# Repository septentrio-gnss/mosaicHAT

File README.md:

# mosaicHAT

mosaicHAT: A GNSS HAT for Raspberry PI </br>
Author: <a href="https://github.com/Jamalhazem98">Jamal Sa'd</a>  </br>
Maintainer: (Septentrio gnss github user) <githubuser@septentrio.com> </br>
External website: https://github.com/septentrio-gnss/mosaicHAT </br>
License: <a href="https://creativecommons.org/licenses/by-sa/4.0/">Creative Commons Attribution Share-Alike License.</a> and <a href="https://www.oshwa.org/definition/">Open Source HW</a> </br>
Available for purchase here: https://www.ardusimple.com/product/septentrio-mosaichat/ </br>

Click to watch this video introducing mosaicHAT

Table of contents
=================
<!--ts-->
   * [Introduction to mosaicHAT](#introduction-to-mosaichat)
      * [What is mosaicHAT?](#what-is-mosaichat)
      * [A HAT for Raspberry Pi?](#a-hat-for-raspberry-pi)
      * [What is the mosaic module?](#what-is-the-mosaic-module)
      * [Who is Septentrio?](#who-is-septentrio)
      * [Is the project Open Source?](#is-the-project-open-source)
      * [mosaicHAT News](#mosaicHAT-News)
      * [Disclaimer](#disclaimer)
   * [mosaicHAT user documentation](#mosaichat-user-documentation)
      * [mosaicHAT Manufacturing and Assembly](#mosaichat-manufacturing-and-assembly)
      * [General interfaces of mosaicHAT](#General-interfaces-of-mosaichat)
      * [Connecting to Raspberry Pi](#connecting-to-raspberry-pi)
      * [Connecting an antenna](#connecting-an-antenna)
      * [USB Communication](#usb-communication)
      * [Serial Communication](#serial-communication)
      * [FTDI-connector](#ftdi-connector)
      * [Indicator LEDs](#indicator-leds)
      * [Reset mosaic](#reset-mosaic)
      * [PPS Output](#pps-output)
      * [Events](#events)
      * [Python Script](#python-script)
      * [ROS support with ROSaic](#ros-support-with-rosaic)
      * [Arduino support for mosaicHAT](#arduino-support-for-mosaichat)
      * [Using the Fritzing Schematics](#using-the-fritzing-schematics)
   * [mosaicHAT Design documentation](#mosaichat-design-documentation)
      * [mosaic Pinout](#mosaic-pinout)
      * [Power Sources](#power-sources)
      * [Antennas](#antennas)
      * [Raspberry Pi Serial](#raspberry-pi-serial)
      * [Reset Input](#reset-input)
      * [Micro USB](#micro-usb)
      * [Events and PPSO](#events-and-ppso)
      * [FTDI](#ftdi)
      * [LEDs](#leds)
      * [Clock Frequency Reference ](#clock-frequency-reference )
   * [Further improvements](#further-improvements)
   
<!--te-->

## Introduction to mosaicHAT
### What is mosaicHAT?
The mosaicHAT is an Open Source GPS/GNSS HW PCB HAT which integrates <a href="https://www.septentrio.com/en/products/gnss-receivers/rover-base-receivers/receivers-module/mosaic">Septentrio's mosaic-X5</a> GNSS module (and other Septentrio pin compatible modules) with basic communications and which can be stacked into a Raspberry Pi system. 

The goal of the design is to allow easy HW prototyping using the mosaic-X5 GNSS module taking the advantage of the computer ecosystem provided by the Raspberry Pi environment. The board however can also be used standalone since it can be powered either via USB or via power pins. 
This project and design can be used either produced with your local electronics assembly house or can also be used as a starting point for your own HW integrations.

### A HAT for Raspberry Pi?
HAT stands for “Hardware Attached on Top”. It is a new hardware specification for add-one modules for the new Raspberry Pi model B+. HATs have several advantages compared to older add-on modules for the Raspberry Pi.

#### Robust mechanical design
With 4 mounting holes the connection between the Raspberry Pi and the add-on board is very robust. 

### Can I buy it?
#### Buy at Ardusimple now
Yes, the mosaicHAT can now be purchased from Ardusimple directly. Ardusimple is a company which produces easy to use GNSS RTK systems. They can sell the mosaicHAT directly as well as other mosaic based GNSS boards.
</br>
Website: https://www.ardusimple.com/product/septentrio-mosaichat/

#### Produce yourself
You can also use the reference design, layout and Bill Of Materials from this project and contact your local manufacturing company for producing it (no restrictions). Within this project we have used [Eurocircuits](https://www.eurocircuits.com/) who can be quite fast in producing a board for you (both PCB and assembly can be done by them). Section [mosaicHAT Manufacturing and Assembly](#mosaichat-manufacturing-and-assembly)

##### Do I need to source special components for producing this board?
Not really, most of the components are generic enough. All components used are available on Digi-Key and clearly listed in the project's Bill Of Materials. The mosaic GNSS module can be obtained from Digikey or directly from Septentrio. Should your project be larger then we recommend you to contact Septentrio sales team directly at <a href="https://www.septentrio.com/en/contact/ask-question">Septentrio Contact Page</a>.

### What is the mosaic module?
#### mosaic-X5
<a href="https://www.septentrio.com/en/products/gnss-receivers/rover-base-receivers/receivers-module/mosaic">Septentrio's mosaic-X5</a>, a multi-band, multi-constellation GNSS receiver in a low power surface mount module with a wide array of interfaces, designed for mass market applications like robotics and autonomous systems, capable of tracking all Global Navigation Satellite System (GNSS) constellations supporting current and future signals. With unique built-in AIM+ technology for interference mitigation, Septentrio is offering a performance benchmark in mass market GNSS positioning building blocks.

#### Other mosaic versions

Any <a href="https://web.septentrio.com/GH-SSN-modules c">other mosaic pin compatible products</a> could also be used on this design, however you would need to take into consideration the functions or pins which would need to exposed and then modify the design for your own project. Surely feel free to spin of the project and refer to this one should you make other open source designs based on mosaicHAT.

### Who is Septentrio?

Septentrio designs, manufactures and sells high-precision, multi-frequency, multi-constellation GPS/GNSS equipment for use in demanding applications. Septentrio products are used in a wide variety of industries including marine, construction, precision agriculture, logistics, machine control, rail, automotive, survey and mapping, geographic information systems (GIS), unmanned aerial vehicles (UAVs) and scientific. Septentrio receivers deliver consistently accurate and precise GNSS positioning scalable to centimeter-level and designed to perform solidly in the most challenging environments. Septentrio receivers are available as OEM boards, housed receivers and smart antennas.

The technology offers high accuracy and reliability thanks to GNSS+ algorithms as well as <a href="https://www.septentrio.com/en/advanced-interference-monitoring-mitigation-aim">Septentrio's Advanced Interference Monitoring and Mitigation (AIM+)</a> which protects against RF interference (jamming) and spoofing.

For more information about Septentrio products go to [**https://www.septentrio.com/**](https://web.septentrio.com/GH-SSN-home).

### Deliverables
This project makes the following deliverables for both integrators and designers of systems around Septentrio's mosaic modules.

|File|Description|
|--------|----------|
|KiCAD_files/HATv1.0.pro| KiCAD project |
|KiCAD_files/HATv1.0.kicad_pcb | KiCAD layout |
|KiCAD_files/HATv1.0.sch| KiCAD schematic |
|KiCAD_files/mosaicHAT_library.lib| Project schematic library |
|mosaic_design_components/mosaic_X5.mosaic-X5.lib | mosaic symbol |
|mosaic_design_components/mosaic_X5.kicad_mod| mosaic footprint |
|mosaic_design_components/mosaic3D.stp| mosaic 3D object |
|BOM/mosaicHAT_BOM.xlsx| mosaicHAT Bill of Materials |
|Fritzing/mosaicHAT.fzpz| mosaicHAT Fritzing part |
|Fritzing/mosaicHAT_Graphic.svg| mosaicHAT SVG |

### Is the project open source?
Yes, as it allows easy adaptations and thus enables the robotics and autonomous community to create their own spin off projects.
As such this can be also a starting reference point for integrators when in need of GNSS integration.

With open source it means that the following is provided:
-Editable source files
-Modifications and spin off projects allowed
-You are allowed to sell your version. No -NC limitations.
-May require attribution
-We encourage you to stand on our shoulders and even make money at it! 

More info about licensing can be found here: 
<a href="https://creativecommons.org/licenses/by-sa/4.0/">Creative Commons Attribution Share-Alike License.</a> and <a href="https://www.oshwa.org/definition/">Open Source HW</a>

### mosaicHAT News
 
#### Survey-grade GNSS receiver based on mosaicHAT, by Chiba Institue of Technologyy.
Low-cost survey-grade GNSS mosaicHAT Station built by Prof. Suzuki from Chiba Institute Of Technology, Japan. The receiver comes with touch display to use the webUI of Septentrio mosaic-X5 GNSS module receiver. Click to visit the project's github repo.

#### Drive test to Dead Sea with RTK corrections 
mosaicHAT has been taken in a GNSS/RTK drive to the lowest point on earth's land - The Dead Sea (-400m Sea Level).
Click to watch the journey on Youtube:

### Disclaimer

This project is **PROVIDED AS IS** and while the general interfaces have been tested, the project has not been fully validated nor by the author nor by Septentrio.
It remains your responsibility when producing or using this design for your own purposes.
We recommend you to contact Septentrio should you have questions on how to integrate Septentrio's GNSS mosaic modules.

Their support web site is <http://www.septentrio.com/support> </br>.

### Documentation sections
This project contains two important sections for documentation. The first one which is a user documentation (see section [mosaicHAT user documentation](#mosaichat-user-documentation)) and the second one (see section [mosaicHAT Design documentation](#mosaichat-design-documentation)) which is a documentation for designers wanting to modify the reference design of this project.

## mosaicHAT user documentation
### mosaicHAT Manufacturing and Assembly
You can use the reference design, layout and Bill Of Materials files from this project and contact your local manufacturing company for producing it. Within this project we have used [Eurocircuits](https://www.eurocircuits.com/) who can be quite fast in producing a board  (both PCB and assembly can be done by them).

#### Elements to provide when manufacturing the board

If you decided to make the board through a PCB manufacturing service, they will ask for the following parts:

For manufacturing the board:

- Layout design (Some services accept native KiCAD files, otherwise you will need to export the layout to the standard Gerber format).

For assembly:

- Bill of Materials (BOM), the list of used electronic components alongside with their reference designators. For our project, check [mosaicHAT BOM](BOM/mosaicHAT_BOM.xlsx).
- Component Placement List (CPL), the exact position of each component on the board (X,Y and Rotation). CPL could be exported from KiCAD however should not be taken for granted. The user have to check with the manufacturing service to ensure the right placement for components.

#### Ordering mosaic
You can order the mosaic-X5 from [Digikey](https://www.digikey.com/en/product-highlight/s/septentrio/mosaic-x5-module) or you can contact Septentrio at <www.septentrio.com> for direct purchasing or for other mosaic models.

|Organization | part number|
|--------|----------|
|Digikey part number | 2771-410322-ND |
|Septentrio part number| 410322|

### General interfaces of mosaicHAT
The board exposes the following interfaces:

### Connecting to Raspberry Pi

mosaicHAT could be easily attached on Raspberry Pi as shown here:

If the direct headers' connections were expanded for illustration, they will look like:

Power connections:

|Wires |Type |
|--------|----------|
|Red | +5V |
|Black | GND|

Communication connections

|Wires |Type |
|--------|----------|
|Blue | Serial UART |
|Orange | General LEDs |
|Purple | Reset |

#### Preparing Raspberry Pi

To enable communication between mosaicHAT and Raspberry Pi (RPi), you should make sure needed communication permissions are set. We've tested mosaicHAT with both Raspbian OS and Ubuntu OS on RPi and found the following points needed.

##### Raspbian OS
- To enable RPi serial communication, go to terminal and run:

  `sudo raspi-config`

- Select **Interfacing Options**, then from the menu select **Serial**. You will get the question:

  *Would you like a login shell to be accessible over serial?*

  Select **No**. Another prompt will ask:

  *Would you like the serial port hardware to be enabled?*

  Select **Yes**.

- Finally, exit the config and reboot RPi for changes to take effect.

##### Ubuntu OS

- To enable RPi's UART, go to `/boot/config.txt` and set `enable_uart=1` at the end of the file. This could be done directly on SD card or using:
 
  `sudo nano /boot/config.txt` 

- You will also need to disable UART console login. To do so on RPi 4, use:

  `sudo nano /boot/firmware/nobtcmd.txt` 

  And delete `console=ttyAMA0,115200` from the file. For different RPi versions, the cmd configuration file could be `/boot/cmdline.txt`.

- Ethernet-over-USB may not be enabled by default. To enable Ethernet-over-USB, go to:

  `sudo nano /etc/network/interfaces`

  And add:
  ```
  allow-hotplug usb0

  iface usb0 inet dhcp
  ```
-  Reboot RPi for changes to take effect.

#### Connecting an antenna
In order to benefit from the multiple signals and constellations that the mosaicHAT board has it is recommended to purchase a capable multiband antenna.
There are several GNSS antenna manufacturers in the market (e.g. Maxtenna, Tallysman, etc). For more information you can also contact Septentrio.

There are also different antenna types each of them suitable for different applications (e.g. robotics, larger machines, etc). Surely the larger the antenna the better performance you might get, however it is not all about size but also quality of antenna elements themselves.

Please make sure you get the right jumper so you can also set the right voltage depending on the chosen GNSS antenna.

Note: mosaicHAT board contains only one voltage regulator (3.3V). The 5V line is directly connected to power sources. As both RPi and USB supply 5V, using them for powering should not impose any threat. However, powering through external power headers should be done carefully. The VANT (Antenna voltage) pad of mosaic module is directly connected to the external +5V pin.  **IT IS NOT PROTECTED AGAINST HIGHER VOLTAGES**. According to mosaic hardware manual, VANT accepts 3V to 5.5V supply.

When using the external power supply, make sure it is not more than 5V. **If more than 5V source is desired, make sure the two PWR jumpers are connected to 3V3 pin, or removed. Supplying higher voltages to VANT could DAMAGE the module.**

In the following photo, a Tallysman antenna has been connected to mosaicHAT. Jumper has been placed to supply 5V to antenna.

_Note: A second antenna connector is added in the mosaicHAT design but the second antenna or heading are not supported with the mosaic-x5 or mosaic-Sx modules. The second antenna connector is only preliminary included for possible future support of heading mosaic modules. It is however important to know that the design with the second antenna connector does not cause any problems when used with the mosaic-x5 or mosaic-Sx modules as long as the main antenna is used (as shown on the picture). Contact Septentrio for more information on dual antenna GNSS receivers._

#### USB Communication

Connecting RPi, as well as any other PC, to mosaic via USB provides:
- Septentrio's web interface
- Two USB serial ports
- Multiple TCP/IP ports

The Windows USB driver provided with mosaicHAT emulates two virtual serial ports, which
can be used as standard COM ports to access the receiver. The Windows USB diver can be
installed through the RxTools software suite. 

Septentrio's RxTools is a SW which can be used to communicate to the mosaicHAT and can be downloaded free of charge from the [Septentrio support site](https://www.septentrio.com/en/support/software/rxtools).

On Linux, the standard Linux CDC-ACM driver is suitable. Most terminal emulation programs will make no distinction between virtual and
native COM ports. Note that the port settings (baud rate, etc) for virtual serial ports are not
relevant, and can be left in their default configuration in the terminal emulation program.
When connecting the USB cable to a Windows PC, a new drive appears in the file manager.
This drive contains an installer for the USB driver. Running this installer is not needed if
you have already installed the RxTools suite. 

When the USB cable is connected, the receiver supports Ethernet-over-USB. The IP address
allocated to the Ethernet-over-USB interface is 192.168.3.1. The Web user interface of the receiver can then be accessed using (http://192.168.3.1).

USB communication with mosaicHAT could be tested using tools like [PuTTY](https://www.putty.org/). For example, here USB1 serial port is accessed to stream NMEA GGA messages:

TCP/IP ports could be also tested using PuTTY, or directly from terminal. Note that 28784 is the default TCP command port: 

`telnet 192.168.3.1 28784`

More information on how to configure or access the web interface, USB serial and USB TCP can be found in the mosaic-X5 reference guide. You can download this one from [Septentrio support site](https://www.septentrio.com/en/support/mosaic/mosaic-x5).

#### Serial Communication

A simple way to communicate with the mosaicHAT receiver is to connect one of its COM-ports.
The mosaicHAT offers 2 COM port connectors:
   * *COM connector to Raspberry-Pi*: The std connector of Raspberry Pi systems offer a serial communication. The mosaic-X5 COM1 port is connected to the Raspberry-Pi for easy integration.
   * *COM on the board (usable for FTDI)*: An extra serial port (COM2 of the mosaic-X5) is exposed via another connector on the board. This port (TTL levels) can be usable as a secondary port or can also be usable to connect an FTDI converter (e.g. serial to Bluetooth or TTL to RS232 converter). See next FTDI section
   
default COM-port settings are:
|Parameter |Value |
|--------|----------|
|baud rate | 115200 |
|data bits| 8|
|parity| no|
|stop bits| 1|
|flow control| none|

The baud rate can be modified at any time by using the **setCOMSettings** command.  

Serial connection between RPi and mosaicHAT could be tested using PuTTY:

- Choose serial connection type **/dev/ttyS0**.
- Write the right baud rate **(default: 115200)**.
- To send commands, force on *Local echo* and *Local line editing* from **Terminal** tab.

Septentrio's RxTools is a SW which can be used to communicate to the mosaicHAT and can be downloaded free of charge from the [Septentrio support site](https://www.septentrio.com/en/support/software/rxtools).
Once you have downloaded it you can use Septentrio's RxControl and Data Link which can communicate with the receiver over a COM-port connection:
select Serial Connection option when opening the connection to the receiver.

Note that currently there's no RxTools release for RPi (ARM architecture). Thus, RxTools should be used on a regular PC.

#### FTDI Connector
As mentioned an extra serial port is made available and can be used as an FTDI. The pins are aligned with standard FTDI conformity thus you can add support for converting the TTL to an RS-232 or USB signals. FTDI can also be used with some Bluetooth devices. There is a large variety of FTDI devices which can help in communicating with the mosaicHAT. 

Example of an FTDI (USB cable)

In the following example, the common Bluetooth module (HC-06) has been used to control mosaicHAT from Android mobile phone. Note that most modules have a default 9600 baud rate while mosaic's default is 115200. Both devices should be set to the same baud rate for proper communication.

mosaicHAT-HC-06 connections:

FTDI connector could be used to convert TTL to RS-232. A more detailed schematic could be found in mosaic Hardware Manual.

TTL to USB connections:

#### Indicator LEDs
The following LEDs are defined on the mosaicHAT:

|LED|Description|
|--------|----------|
|PWR | Device State (ON/OFF) |
|PPS | Pulse Per Second |
|GL1 | Connected to RPi (GPIO 6) |
|GL2 | Connected to RPi (GPIO 26) |
|PVT | PVT Available |

PPSO clock could be tuned using **setPPSParameters** command. While GPLED default mode is *PVTLED*, it could be configured to work in different modes (*PVTLED*, *DIFFCORLED* and *TRACKLED*) using **setLEDMode** command. Refer to the Hardware Manual for blinking behaviour of each mode. Both General Purpose LEDs (GL1 and GL2) could be directly controlled by Raspberry Pi GPIO.

Just for illustration, the following python script runs GL1 and GL2 in alternate blinking mode. It is up to users to customize those LEDs as convenient for their applications. 

```
import RPi.GPIO as GPIO # Import Raspberry Pi GPIO library
from time import sleep # Import the sleep function from the time module

GPIO.setwarnings(False) # Ignore warning for now
GPIO.setmode(GPIO.BCM) # Use BCM pin numbering

# Set pins 6 &26 to be output pins and set their initial values to low (off)
GPIO.setup(26, GPIO.OUT, initial=GPIO.LOW) 
GPIO.setup(6, GPIO.OUT, initial=GPIO.LOW) 

while True: # Run forever
 GPIO.output(26, GPIO.HIGH) # Turn 26 on
 GPIO.output(6, GPIO.LOW) # Turn 26 off
 sleep(1) # Sleep for 1 second
 GPIO.output(26, GPIO.LOW) # Turn 26 off
 GPIO.output(6, GPIO.HIGH) # Turn 6 on
 sleep(1) # Sleep for 1 second
```

#### Reset mosaic

mosaic-X5 could be forced to reset from Raspberry Pi. The nRST_IN pin of mosaic is directly connected to RPi GPIO 5 (Pin 29 in physical header).

The nRST_IN pin is active negative, which means mosaic will be in RESET mode when nRST_IN is low (GND). The pin is internally debounced (pull-up) so if pin is left unconnected (floating) the module will not enter RESET mode.

Initially, the RPi GPIO pins are set to INPUT mode. As the RPi input line have high impedance, nRST_IN will be floating. This means mosaicHAT board could run without issues initially even if GPIO 5 is not set to HIGH (while kept in input mode). However, it is not recommended to rely on the GPIO initial state. Users should drive HIGH to GPIO 5 for the stability of their applications.

To reset module, a LOW pulse, not shorter than 1 microsecond, should be driven to GPIO 5. 

#### PPS Output
PPS signals are used for precise timekeeping and time measurement. One increasingly common use is in time synchronization with other sensors (e.g. Lidars or IMUs). 

The receiver is able to generate an x-pulse-per-second (xPPS) signal aligned with either GPS, Galileo or GLONASS system time, or with UTC, or with the internal receiver time (RxClock). RxClock could be used to test PPS if no antenna or PVT available.

 Polarity, frequency and pulse width of PPSO could be configured by **setPPSParameters** command. 

PPS Output runs on 3.3V level. PPSO is directly connected to an indicator LED. While most PPS applications require a short pulse width, you may need to increase the pulse width to notice LED blinking.
  
More information on the definition of PPS output or on how to configure the PPS parameters can be found in the mosaic-X5 reference guide. You can download this one from [Septentrio support site](https://www.septentrio.com/en/support/mosaic/mosaic-x5).

#### Events
The receiver can time-tag electrical level transitions on its Event input with an accuracy of 20ns.
By default, the receiver reacts on low-to-high transitions but can also be configured on the receiver using **setEventParameters** command.
Upon detection of a transition, the receiver can output the time and/or the position at the instant of the event. This will be output in the Septentrio Binary Format.

Events can be used as an example for UAV Photogrammetry (tagging the pictures taken either by a UAV or a robot).

EVENTs could be tested directly on mosaicHAT board by connecting PPS Output to one of the EVENTs pins. Note that this works with a single wire because they share the same GND. Here EVENTA is connected to PPSO, with PPS interval set to 1 sec. 

To monitor EVENTs through web interface, go to PPS/Timing from GNSS menu:

EVENTs run on 3.3V level.

More information on the Events input of mosaic-X5 can be found in the mosaic-X5 reference guide. You can download this one from [Septentrio support site](https://www.septentrio.com/en/support/mosaic/mosaic-x5).

### Python Script

Following is a sample python script that could run on RPi to read coordinates from mosaicHAT. The script streams NMEA GGA messages from mosaic via serial, parse them and prints out coordinates.

```
import serial
import time

# Establish serial connection
ser = serial.Serial('/dev/ttyS0', 115200)
# /dev/ttyS0 is the RPi UART, 115200 is mosaic default baud rate
# For USB Serial, this could be (/dev/ttyACM0),the number is not fixed, to check your ports run: dmesg | grep tty
# Your application may not have access to USB serial, if you got an error run: sudo chmod 666 /dev/ttyACM0
time.sleep(1) # Wait for connection
ser.write(b'SSSSSSSSSSSSS\n') # Push mosaic to run in command mode
time.sleep(0.1) 
ser.write(b'sno, Stream1, COM1, GGA, sec1\n') # starting NMEA GGA stream command, for USB replace COM1 with USB1 or USB2
time.sleep(0.1)

while True:
    nmea_bytes = ser.readline()        
    nmea_string = str(nmea_bytes.decode())  
    nmea_string = nmea_string.rstrip()
    if (nmea_string.startswith('$GPGGA')):

        nmea_array = [element.strip() for element in nmea_string.split(',')]
        Quality_Indicator = int(nmea_array[6])
        if Quality_Indicator==0:
            print("No GPS Fix Available!") # NMEA GGA Quality indicator = 0 means no fix available
        else:
            # Parse NMEA GGA message
            UTC_Time= float(nmea_array[1])
            Latitude= float(nmea_array[2])*0.01
            Latitude_direction = nmea_array[3]
            Longitude = float(nmea_array[4])*0.01
            Longitude_direction = nmea_array[5]
            Height = float(nmea_array[9])
            Height_unit = nmea_array[10]
            # Print coordinates
            print('UTC Time: ' + str(UTC_Time))
            print(' Latitude: ' + str(Latitude) + Latitude_direction)
            print(' Longitude: ' + str(Longitude) + Longitude_direction)
            print(' Height: ' + str(Height) + Height_unit)  
        time.sleep(0.1)
    else:
        continue         

ser.close()

```

#### ROS support with ROSaic

The mosaic-X5 but also mosaicHAT are supported by ROSaic. ROSaic is a ROS driver for the mosaic modules and allows you to do integrations for robotic applications.
ROSaic is also an open source project and can be found here:

   * ROS Wiki : [http://wiki.ros.org/septentrio_gnss_driver](http://wiki.ros.org/septentrio_gnss_driver)
   
   * Github : [https://github.com/septentrio-gnss/septentrio_gnss_driver](https://github.com/septentrio-gnss/septentrio_gnss_driver)

#### Arduino support for mosaicHAT

The mosaicHAT can also work with Arduino. Take a look at the following project at Instructables.
mosaicHAT Arduino is also an open source project and can be found here:

   * Instructables page : [https://www.instructables.com/Building-a-GNSS-Receiver-Using-MosaicHAT-and-Ardui/](https://www.instructables.com/Building-a-GNSS-Receiver-Using-MosaicHAT-and-Ardui/)
   
   * Github : [https://github.com/septentrio-gnss/mosaicHAT_Arduino_receiver](https://github.com/septentrio-gnss/mosaicHAT_Arduino_receiver)

#### Using the Fritzing Schematics
[Fritzing](https://fritzing.org/) is an open-source hardware initiative that makes electronics accessible as a creative material for anyone. They offer a software tool, a community website and services in the spirit of using among others Arduino and to facilitate the layout and manufacturing of professional pcbs.

mosaicHAT fritzing part could be downloaded from [here](Fritzing). Drag and drop the *.fzpz* file into fritzing interface or import through File>Open from the Menu Bar. With breadboard, schematic, and layout views designers can have a clear intuition on how the project will work and look like.

## mosaicHAT Design documentation

This section is intended for people who want to understand more about the design of the mosaicHAT.

### Design Overview
mosaicHAT is a 4-Layer Printed Circuit Board (PCB) designed to stack on top of Raspberry Pi. Both Top and Back layers are used for power and signals. The first inner layer is a GND plane whereas the second inner layer functions as a 3.3V power plane with a slight use of other connections.

Other than the female Raspberry Pi connecter, all components are placed on the Top layer. All components are Surface Mount Devices (SMD) except for connectors.

mosaicHAT was designed using [KiCAD](https://kicad.org), an open source suite for Electric Design Automation. KiCAD provides a beautiful 3D viewer besides its design capabilities.

Following is the schematic plan, for higher quality check [PDF schematic](mosaicHAT_schematic.pdf).

The board layout, hiding filled areas in zones. 

Following is the layout layers description:

|Layer|Description|
|--------|----------|
|Layer 1| Red traces, trace free zones are filled with GND copper pour |
|Layer 2 | Full GND plane |
|Layer 3| Pink traces, trace free zones make a 3.3V power plane |
|Layer 4| Green traces, trace free zones are filled with GND copper pour |

A top 3D view of mosaicHAT, featuring main electronic components.

The following sections provide more details on mosaicHAT design.

### mosaic Pinout

Septentrio mosaic-X5 is the base of mosaicHAT board. mosaic is a 31x31mm LGA module with 239 pins. All needed information on mosaic connections could be found in the [Hardware Manual](References/mosaic_hardware_manual_v1.3.0.pdf) 

KiCAD symbol, footprint and a 3D model of mosaic could be found in folder [mosaic Design Components](mosaic_design_components).

Following the manual instructions:

- The 3.3V DC supply is connected to all VDD_3V3 pins and to the VDD_BAT pin. A decoupling capacitor has been used.
- All ground pins are connected to GND.
- 1V8_OUT is connected to SYNC.
- Pin A3 (RTC_XTALI) is connected to GND.
- Pin AB7 (Reserved_GND) is connected to GND.
- All "Reserved_NC" pins are left unconnected.
- Other unused functions pins are left unconnected.

Note that a second un-assembled capacitor place has been left for debugging and testing. The second capacitor is not necessary for the function of mosaicHAT.

### Power Sources

mosaicHAT could be powered through three options; Raspberry Pi, Micro USB and external power pin headers. mosaic module itself runs on 3.3V, thus a voltage regulator is used (LD1117AS33TR). According to its datasheet, the regulator's maximum input is 15V. Raspberry Pi and Micro USB already provide 5V. User should be careful when connecting higher voltage to external power pin headers. Though 5V is preferable, user can input up to 15V only if both VANT and FTDI PWR SRC jumpers are unconnected or connected to 3.3V. Pin headers of 5V in the jumpers are connected directly to input sources as it's presumed to be 5V.
                   
Note: It is recommended to isolate external power sources from mosaic pads. Adding a dedicated 5V regulator is a safer option if 5V antenna supply is needed. **Supplying higher voltages to VANT could DAMAGE the module.**

Schottky diodes (MBRX120LF-TP) are used to insure one-way current direction. Decoupling capacitors (100nF and 10uF) are used according to regulator’s datasheet. Following is the power part of schematic.

In the figure above:

1. Voltage Regulator (LD1117AS33TR).

2. Raspberry Pi power source (5V pins).

3. External power source headers.

4. Micro USB power source.

### Antennas

As mentioned before, mosaic-X5 is a single antenna module. Second antenna is preliminary included for possible future modules. Only first antenna (ANT1) is needed for the function of mosaicHAT.

Following is the antennas part in schematic.

#### First Antenna
The first antenna SMA connector is directly connected to ANT1 pad. ANT1 is ESD-protected within the module and carries DC voltage. The DC voltage of ANT1 is supplied from mosaic's VANT pad. mosaicHAT user could choose between 3.3V and 5V supply to VANT using 2.00 mm header jumpers.

The nominal input impedance of the RF line is 50 Ohms. Thus, antenna trace should have a characteristic impedance (Zo) of 50 Ohms. Line impedance could be measured by different tools, such as the freeware [Saturn PCB toolkit](https://saturnpcb.com/pcb_toolkit).

Right characteristic impedance (~50 Ohms) could be reached by adjusting the width of RF line (Conductor Width) having PCB specifications fixed. Frequency is set to 1575 MHz as the GPS L1 Frequency. Conductor Hight is the thickness of the dielectric material between Top layer and the next copper layer which depends on manufacturing service and board specifications, in mosaicHAT case it's 0.36 mm.

Having right characteristic impedance insures reduced reflections in the opposite direction thus higher quality of signals. For uniform lines, characteristic impedance is not dependent on trace length.

It is also important to stich vias every few millimeters around the RF line for good ground coherence. Stitching GND vias help to protect line from interference.

For more details on antennas and interference please refer to mosaic's [Hardware Manual](mosaicHAT/References/mosaic_hardware_manual_v1.3.0.pdf).

Following is the first antenna part of board layout. The center of SMA connector is copper freed to prevent undesired capacitance due to high copper density.

#### Second Antenna
_Note: A second antenna connector is added in the mosaicHAT design but the second antenna or heading are not supported with the mosaic-x5 or mosaic-Sx modules. The second antenna connector is only preliminary included  for possible future support of heading mosaic modules. It is however important to know that the design with the second antenna connector does not cause any problems when used with the mosaic-x5 or mosaic-Sx modules as long as the main antenna is used. Contact Septentrio for more information on dual antenna GNSS receivers. The design below is preliminary but is subject to change upon release of future Septentrio mosaic dual antenna modules._

The second antenna is similar to first antenna except that ANT2 pad in mosaic is not internally ESD-protected and does not carry DC voltage by itself. Wherefore, both protection and DC biasing are needed.

For ESD protection, TVS diode (SESD0402X1BN-0010-098) is used. TVS diode protects the module against sudden removal of the antenna. As any stubs branching out of the RF line could cause undesired reflections, TVS diode should be placed exactly on top of the RF trace.

Biasing inductors are used to supply the ANT2 with DC voltage from ANT1 trace. Two inductors, one for each RF line, are used to avoid stubs and provide single tracks for RF signals. The inductor value is best to be around 33 nH with self-resonant frequency of 1.4 GHz. A 100 nF bypass capacitor has been placed between inductors to filter out any AC noise.

In the figure above:

1. ANT1 RF trace.

2. DC biasing circuit.

3. ANT2 RF trace.

4. VANT source jumper 2.00 mm headers.

5. TVS diode.

  6 &7. SMA female connectors (Amphenol 132136).

### Raspberry Pi Serial

Serial communication with Raspberry Pi is conducted by connecting COM1 of mosaic to Raspberry Pi UART pins: TX (GPIO 14) and RX (GPIO 15). GPIO 14 is pin 8 on the GPIO header whereas GPIO 15 is pin 10. Raspberry Pi's TX is connected to mosaic's RX1 while RX is connected to mosaic's TX1.

According to the hardware manual, non-zero voltage should not be driven to mosaic's input pads while in standby mode.

Thus, MosaicRX1 signal has been tri-stated by MODULE_RDY using tri-state buffer (SN74LVC1G126DRLR). 

### Reset Input

The nRST_IN pin of mosaic is directly connected to RPi GPIO 5 (Pin 29 in physical header). Refer to [Reset mosaic](#reset-mosaic) in user documentation for more details.

### Micro USB

To use mosaic as a USB device, the following pins of the module should be connected to a USB connector.

A common mode filter with ESD protection for USB 2.0 (ECMF02-2AMX6) is used with USB_DEV_P (D+) and USB_DEV_N (D-) for protection. The filter suppresses the noise of electromagnetic interference (EMI) on high speed differential USB lines.  

As USB uses a differential pair, differential pair impedance (Zdifferential) should be tuned to avoid reflections. Zdifferential needs to be around 90 Ohms. Zdifferential could be calculated using Saturn's PCB toolkit. For mosaicHAT USB, traces width was set to 0.35 mm with 0.15 mm spacing.

Following board figure shows USB parts highlighted. GND vias were stitched around the USB connector and lines to insure good ground coherence. 

1. Micro USB connector (Molex 1050170001).

2. Common mode filter.

3. USB D+/D- lines.

4. USB_V.

### Events and PPSO

mosaic offers two event inputs which could be used to time tag external events. Both input pads of mosaic, EVENTA and EVENTB, use 1.8V level. For better integration with external applications, a level shifter (SN74AVC4T245PWR) is used to transform signals into 3.3V level.

Pulse Per Second Output (PPSO) is a mosaic clock output. Polarity, frequency and pulse width of PPSO could be configured by **setPPSParameters** command. As PPSO uses 1.8V level as well, same level shifter is used to get 3.3V level signals.

Both EVENTS and PPSO 3.3V levels are connected to 2.54 mm pin headers.

Port A tracks 1.8V while port B tracks 3.3V level. Direction could be set for two channels, each provides two connections. (1DIR) is set to low for mosaic input direction while (2DIR) is set to high for output direction. Both (O̅E̅) pins are set to low to enable low impedance state. VCCB is connected to +3.3V while VCCA is connected to +1.8V, which is supplied by 1V8_OUT pin of mosaic. Bypass capacitors are used on power supplies according to datasheet.

1. EVENTS, PPSO and 1V8_OUT vias, connected to level shifter via Back layer.

2. Level shifter.

3. 3.3V level pin headers.

### FTDI

Second serial connection to mosaic (COM2) is exposed through 2.54 mm pin headers. The FTDI connection could be used to communicate with other devices through serial (e.g. HC-06 Bluetooth module).

If the device needs power supply from mosaicHAT, like HC-06, VCC pin of FTDI could be used. 5V or 3.3V could be provided by moving The FTDI PWR SRC jumpers.

### LEDs

mosaicHAT comes with five blue indicator LEDs.

1. Raspberry Pi's (GPIO 6) which is pin 31 in header, connected to GL1 LED. 

2. Raspberry Pi's (GPIO 26) which is pin 37 in header, connected to GL2 LED. 

3. PPSO 3.3V level, connected to PPS LED.  

4. Trace to mosaic's GPLED pin, connected to PVT LED.  

5. Indicator LEDs, PWR LED is directly connected to 3.3V power plane. 

### Clock Frequency Reference 

mosaic module embeds an internal Temperature Compensated Crystal Oscillator (TCXO) for frequency reference. The module can either use its internal TCXO frequency reference or an external frequency reference. In mosiacHAT's case, internal reference is used. 

Following are  Hardware Manual instructions for using internal TCXO.

Layout connections for REF and 2V8.

## Further improvements
Further improvements or recommendations on this project are welcome either here or on spinoff projects.
Here some possible improvements to the current design.
   * Addition of logging capabilities
   * Addition of I2C communication or similar to aid further HAT stacks
   * Further support for mosaic-T receiver (proper timing signals exposure)
   * Communication module (to aid corrections input)
   * Addition of Ethernet communication
   * A 3D housing enclosure on the mosaicHAT for easy tests
   * More open source scripts for communication

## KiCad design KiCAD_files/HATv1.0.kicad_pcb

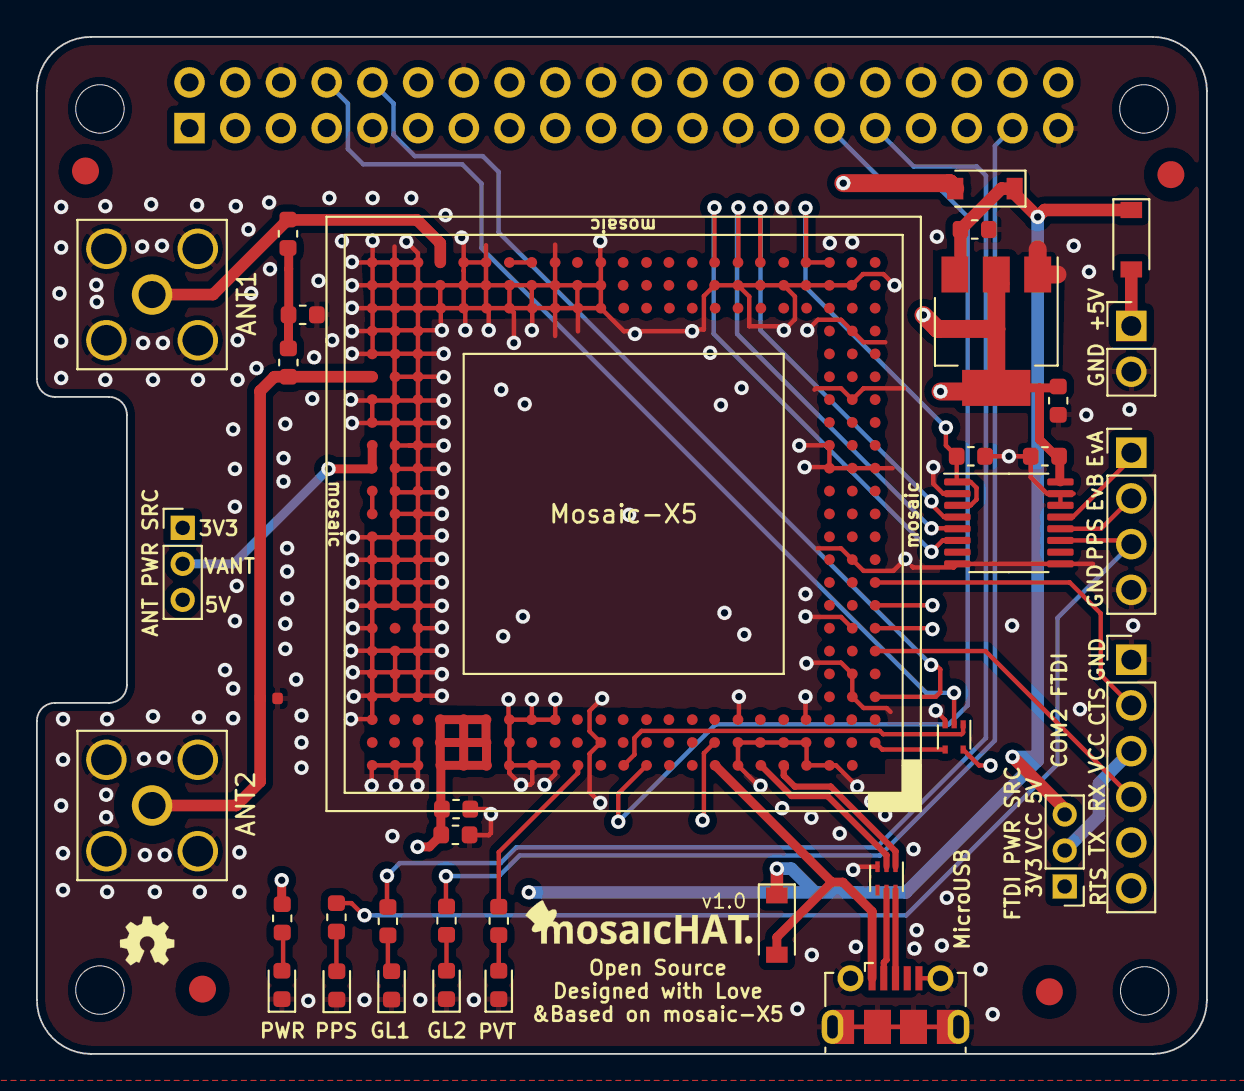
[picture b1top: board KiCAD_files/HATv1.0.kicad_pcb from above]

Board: 4 copper layers, 65.0 x 56.5 mm, 41 parts (1 on the bottom side), 41 nets.

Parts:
C1, C3, C4, C5: 100nF; C_0603_1608Metric
C2, C6: 10uF; C_0603_1608Metric
C7: un-assembled; C_0603_1608Metric
D1, D2, D3: MBRX120LF-TP; D_SOD-123
D4, D5, D6, D7, D8: LED; LED_0603_1608Metric
D9: D_TVS; R_0402_1005Metric
FID1, FID2, FID3, FID4: Fiducial; Fiducial_1.5mm_Mask3mm
FL1: ECMF02-2AMX6; ST_UQFN-6L_1.5x1.7mm_Pitch0.5mm
J1, J2: Conn_Coaxial; SMA_Amphenol_132203-12_Horizontal
J3: USB_B_Micro; USB_Micro-B_Molex-105017-0001
J4: raspberrypi_hat_OX40HAT; PinSocket_2x20_P2.54mm_Vertical
J5: Conn_01x04_Male; PinHeader_1x04_P2.54mm_Vertical
J6: Conn_01x06_Male; PinHeader_1x06_P2.54mm_Vertical
J7: Conn_01x02_Male; PinHeader_1x02_P2.54mm_Vertical
JP1, JP2: Jumper_NC_Dual; PinHeader_1x03_P2.00mm_Vertical
L1, L2: 39nH; L_0603_1608Metric
R1, R2, R3, R4, R5: R330; R_0603_1608Metric
U1: mosaic-X5; mosaic_X5
U2: LD1117AS33TR; SOT-223
U3: SN74AVC4T245PW; TSSOP-16_4.4x5mm_P0.65mm
U4: SN74LVC1G126DRLR; SOT-553

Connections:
+1V8: C4.1, U1.AC3, U1.AC4, U3.1, U3.3
+3V3: C2.1, C5.1, C6.1, C7.1, JP1.1, JP2.1, R1.2, U1.A18, U1.A19, U1.A20, U1.B8, U1.B18, U1.B19, U1.B20, U1.C18, U1.C19, U1.C20, U2.2, U3.16, U4.5
+5V: C1.1, D1.1, D2.1, D3.1, JP1.3, JP2.3, U2.3
/2V8: U1.M23, U1.N23
/ANT1: J1.1, L1.1, U1.AC20
/ANT2: D9.2, J2.1, L2.2, U1.V23
/D+: FL1.6, J3.3
/D-: FL1.5, J3.2
/EVENTA_1V8: U1.AC6, U3.4
/EVENTA_3V3: J5.1, U3.13
/EVENTB_1V8: U1.AC7, U3.5
/EVENTB_3V3: J5.2, U3.12
/External_5V: D3.2, J7.1
/FTDI_PWR: J6.3, JP2.2
/GPLED: R5.2, U1.A14
/MODULE_RDY: U1.A12, U4.1
/MosaicCTS2: J6.2, U1.J1
/MosaicRTS2: J6.6, U1.G1
/MosaicRX1: J4.8, U4.2
/MosaicRX1_BufferOUT: U1.B1, U4.4
/MosaicRX2: J6.4, U1.F1
/MosaicTX1: J4.10, U1.D1
/MosaicTX2: J6.5, U1.H1
/PPSO_1V8: U1.AC8, U3.6
/PPSO_3V3: J5.3, R2.2, U3.11
/REF: U1.AC16, U1.AC17
/RPI_GP1: J4.31, R3.2
/RPI_GP2: J4.37, R4.2
/RPI_P5V: D2.2, J4.2, J4.4
/USB_N: FL1.2, U1.A6
/USB_P: FL1.1, U1.A5
/USB_V: D1.2, J3.1, U1.A8
/VANT: JP1.2, U1.P23, U1.R23
/nRST_IN: J4.29, U1.A11
GND: C1.2, C2.2, C3.2, C4.2, C5.2, C6.2, C7.2, D4.1, D5.1, D6.1, D7.1, D8.1, D9.1, FL1.3, J1.2, J2.2, J3.5, J3.6, J4.6, J4.9, J4.14, J4.20, J4.25, J4.30, J4.34, J4.39, J5.4, J6.1, J7.2, U1.A3, U1.A4, U1.A7, U1.A15, U1.A16, U1.A17, U1.A21, U1.A22, U1.A23, U1.AA13, U1.AA14, U1.AA15, U1.AA16, U1.AA17, U1.AA18, U1.AA19, U1.AA20, U1.AA21, U1.AA22, U1.AA23, U1.AB2, U1.AB3, U1.AB4, U1.AB5, U1.AB6, U1.AB7, U1.AB8, U1.AB13, U1.AB14, U1.AB15, U1.AB16, U1.AB17, U1.AB18, U1.AB19, U1.AB20, U1.AB21, U1.AB22, U1.AB23, U1.AC13, U1.AC15, U1.AC18, U1.AC19, U1.AC21, U1.AC22, U1.AC23, U1.B4, U1.B5, U1.B6, U1.B7, U1.B13, U1.B17, U1.B21, U1.C4, U1.C7, U1.C15, U1.C16, U1.C17, U1.C23, U1.D2, U1.D21, U1.D22, U1.D23, U1.E2, U1.E21, U1.E22, U1.E23, U1.F21, U1.F22, U1.F23, U1.G2, U1.G21, U1.G23, U1.H21, U1.H22, U1.H23, U1.J21, U1.J22, U1.J23, U1.K2, U1.K21, U1.K22, U1.K23, U1.L21, U1.L22, U1.L23, U1.M21, U1.M22, U1.N21, U1.N22, U1.P1, U1.P2, U1.P3, U1.P21, U1.P22, U1.R3, U1.R21, U1.R22, U1.T21, U1.T22, U1.T23, U1.U2, U1.U21, U1.U22, U1.U23, U1.V21, U1.V22, U1.W21, U1.W22, U1.W23, U1.Y2, U1.Y21, U1.Y22, U1.Y23, U2.1, U3.2, U3.8, U3.9, U3.14, U3.15, U4.3
unnamed: C3.1, L1.2, L2.1
unnamed: D4.2, R1.1
unnamed: D5.2, R2.1
unnamed: D6.2, R3.1
unnamed: D7.2, R4.1
unnamed: D8.2, R5.1

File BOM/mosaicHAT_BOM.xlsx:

Reference | Quantity | Value | MPN | SPN | Digi-Key URL
C2 C6 | 2 | 10uF | CC0603KRX5R6BB106 | 311-1782-1-ND | https://www.digikey.com/product-detail/en/yageo/CC0603KRX5R6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
C5 C4 C3 C1 | 4 | 100nF | CC0603KRX7R6BB104 | 311-4055-1-ND | https://www.digikey.com/product-detail/en/yageo/CC0603KRX7R6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
D2 D1 D3 | 3 | MBRX120LF-TP | MBRX120LF-TP | MBRX120LF-TPMSCT-ND | https://www.digikey.com/product-detail/en/micro-commercial-c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
D8 D4 D5 D6 D7 | 5 | LED | TLMB1100-GS08 | SESD0402X1BN-0010-098CT-ND | https://www.digikey.com/product-detail/en/littelfuse-inc/SES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
D9 | 1 | D_TVS | SESD0402X1BN-0010-098 | SESD0402X1BN-0010-098CT-ND | https://www.digikey.com/product-detail/en/littelfuse-inc/SES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
FL1 | 1 | ECMF02-2AMX6 | ECMF02-2AMX6 | 497-10773-1-ND | https://www.digikey.com/product-detail/en/stmicroelectronics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
J1 J2 | 2 | Conn_Coaxial | 132136 | ACX1232-ND | https://www.digikey.com/product-detail/en/amphenol-rf/132136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
J3 | 1 | USB_B_Micro | 1050170001 | WM1399CT-ND | https://www.digikey.com/product-detail/en/molex/1050170001/W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
J4 | 1 | raspberrypi_hat_OX40HAT | 2223 | 1528-1385-ND | https://www.digikey.com/product-detail/en/adafruit-industrie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
J5 | 1 | Conn_01x04_Male | 61300411121 | 732-5317-ND | https://www.digikey.com/product-detail/en/w%C3%BCrth-elektro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
J6 | 1 | Conn_01x06_Male | 61300611121 | 732-5319-ND | https://www.digikey.com/product-detail/en/w%C3%BCrth-elektro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
J7 | 1 | Conn_01x02_Male | 61300211121 | 732-5315-ND | https://www.digikey.com/product-detail/en/w%C3%BCrth-elektro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
JP1 JP2 | 2 | Jumper_NC_Dual | 2PH1-03-UA | 2057-2PH1-03-UA-ND | https://www.digikey.com/product-detail/en/adam-tech/2PH1-03-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
L1 L2 | 2 | 39nH | 744786139A | 732-6270-1-ND | https://www.digikey.com/product-detail/en/w%C3%BCrth-elektro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
R5 R1 R2 R3 R4 | 5 | R330 | ERJ-3EKF3300V | P330HCT-ND | https://www.digikey.com/product-detail/en/panasonic-electron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
U1 | 1 | mosaic-X5 | 410322 | 2771-410322-ND | https://www.digikey.com/en/products/detail/septentrio-inc/41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
U2 | 1 | LD1117AS33TR | LD1117AS33TR | 497-1228-1-ND | https://www.digikey.com/product-detail/en/stmicroelectronics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
U3 | 1 | SN74AVC4T245PW | SN74AVC4T245PWR | 296-18056-1-ND | https://www.digikey.com/product-detail/en/texas-instruments/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
U4 | 1 | SN74LVC1G126DRLR | SN74LVC1G126DRLR | 296-18013-1-ND | https://www.digikey.com/product-detail/en/texas-instruments/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

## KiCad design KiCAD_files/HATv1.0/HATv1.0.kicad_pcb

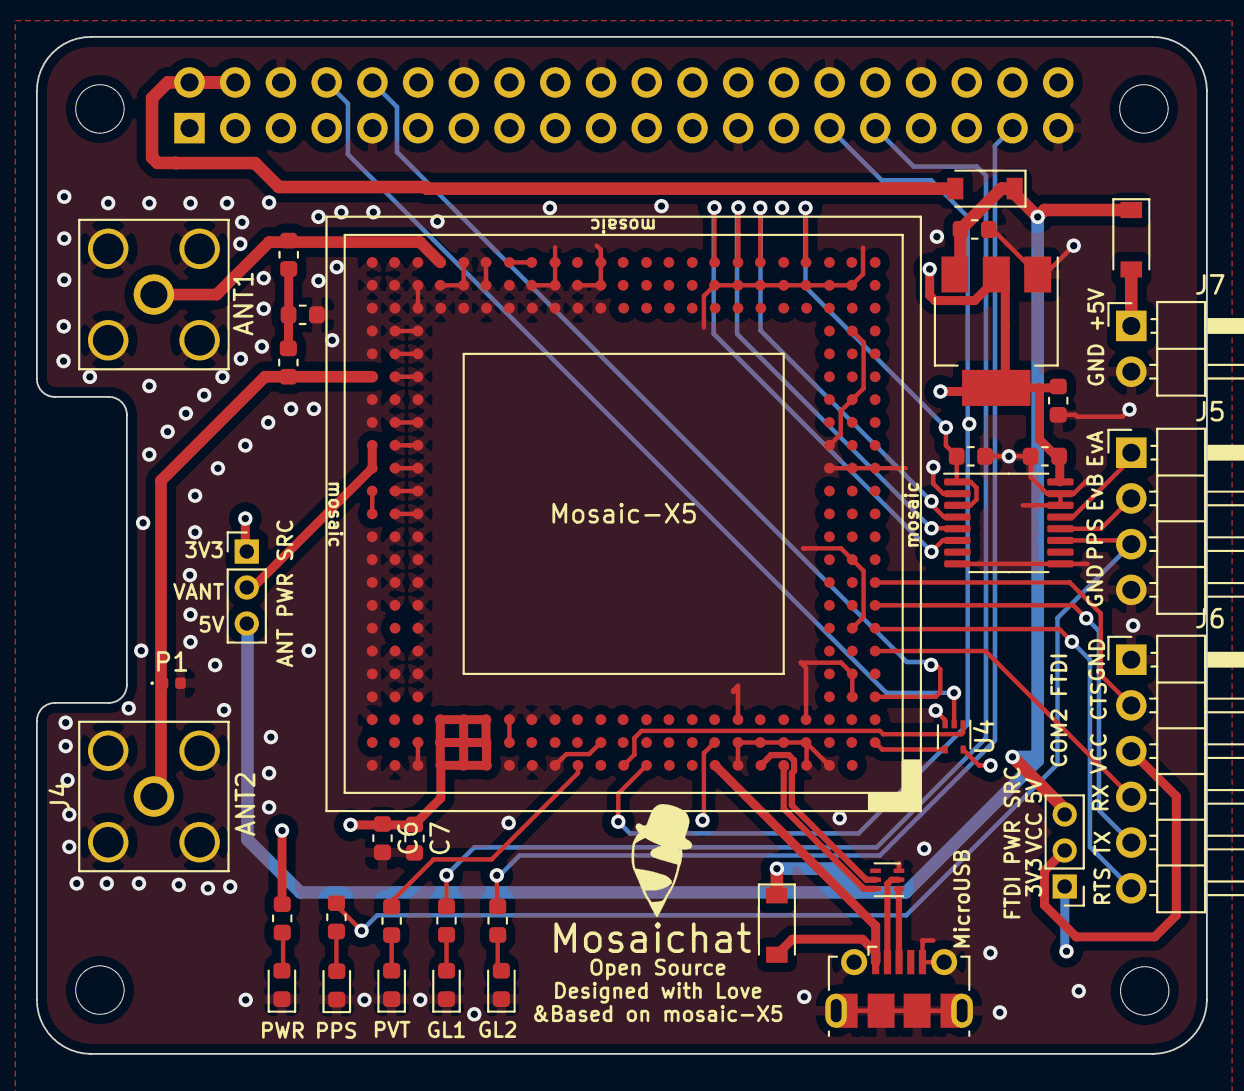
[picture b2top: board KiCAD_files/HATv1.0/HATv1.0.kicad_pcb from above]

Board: 4 copper layers, 65.0 x 56.5 mm, 37 parts (1 on the bottom side), 41 nets.

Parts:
C1, C2, C3, C5: 100nF; C_0603_1608Metric
C4, C6, C7: 10uF; C_0603_1608Metric
D1, D2, D5: MBR0520LT; D_SOD-123
D3, D4, D6, D7, D8: LED; LED_0603_1608Metric
FL1: ECMF02-2AMX6; ST_UQFN-6L_1.5x1.7mm_Pitch0.5mm
J1: USB_B_Micro; USB_Micro-B_Molex-105017-0001
J2: raspberrypi_hat_OX40HAT; PinSocket_2x20_P2.54mm_Vertical
J3, J4: Conn_Coaxial; SMA_Amphenol_132203-12_Horizontal
J5: Conn_01x04_Male; PinHeader_1x04_P2.54mm_Horizontal
J6: Conn_01x06_Male; PinHeader_1x06_P2.54mm_Horizontal
J7: Conn_01x02_Male; PinHeader_1x02_P2.54mm_Horizontal
JP1, JP2: Jumper_NC_Dual; PinHeader_1x03_P2.00mm_Vertical
L1, L2: L; L_0603_1608Metric
P1: TVS; D_0402_1005Metric
R3, R4, R5, R7: R330; R_0603_1608Metric
R6: R; R_0603_1608Metric
U1: SN74AVC4T245PW; TSSOP-16_4.4x5mm_P0.65mm
U2: Mosaic_v0.12; MinROSv0.12
U3: LD1117S33TR_SOT223; SOT-223-3_TabPin2
U4: NiceBuffer; SOT-553

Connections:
+1V8: C2.1, U1.1, U1.3, U2.AC4
+3V3: C3.1, C4.1, C6.1, C7.1, JP1.1, JP2.1, R4.2, U1.16, U2.A18, U2.A19, U2.A20, U2.B8, U2.B18, U2.B19, U2.B20, U2.C18, U2.C19, U2.C20, U3.2, U4.5
+5V: C1.1, D1.1, D2.1, D5.1, JP1.3, JP2.3, U3.3
/ANT1: J3.1, L1.1, U2.AC20
/ANT2: J4.1, L2.2, P1.1, U2.V23
/D+: FL1.1, J1.3
/D-: FL1.2, J1.2
/EVENTA_1V8: U1.4, U2.AC6
/EVENTA_3V3: J5.1, U1.13
/EVENTB_1V8: U1.5, U2.AC7
/EVENTB_3V3: J5.2, U1.12
/External_5V: D5.2, J7.1
/FTDI_PWR: J6.3, JP2.2
/GPLED: R3.2, U2.A14
/MODULE_RDY: U2.A12, U4.1
/MosaicCTS2: J6.2, U2.J1
/MosaicRTS2: J6.6, U2.G1
/MosaicRX1: J2.8, U4.2
/MosaicRX1_BufferOUT: U2.B1, U4.4
/MosaicRX2: J6.4, U2.F1
/MosaicTX1: J2.10, U2.D1
/MosaicTX2: J6.5, U2.H1
/PPSO_1V8: U1.6, U2.AC8
/PPSO_3V3: J5.3, R5.2, U1.11
/RPI_GP1: J2.37, R7.2
/RPI_GP2: J2.31, R6.2
/RPI_P5V: D2.2, J2.2, J2.4
/USB_N: FL1.5, U2.A6
/USB_P: FL1.6, U2.A5
/USB_V: D1.2, J1.1, U2.A8
/VANT: JP1.2, U2.P23, U2.R23
/nRST_IN: J2.29, U2.A11
GND: C1.2, C2.2, C3.2, C4.2, C5.2, C6.2, C7.2, D3.1, D4.1, D6.1, D7.1, D8.1, FL1.3, J1.5, J1.6, J2.6, J2.9, J2.14, J2.20, J2.25, J2.30, J2.34, J2.39, J3.2, J4.2, J5.4, J6.1, J7.2, P1.2, U1.2, U1.8, U1.9, U1.14, U1.15, U2.A3, U2.A4, U2.A7, U2.A15, U2.A16, U2.A17, U2.A21, U2.A22, U2.A23, U2.AA13, U2.AA14, U2.AA15, U2.AA16, U2.AA17, U2.AA18, U2.AA19, U2.AA20, U2.AA21, U2.AA22, U2.AA23, U2.AB2, U2.AB3, U2.AB4, U2.AB5, U2.AB6, U2.AB7, U2.AB8, U2.AB13, U2.AB14, U2.AB15, U2.AB16, U2.AB17, U2.AB18, U2.AB19, U2.AB20, U2.AB21, U2.AB22, U2.AB23, U2.AC13, U2.AC15, U2.AC18, U2.AC19, U2.AC21, U2.AC22, U2.AC23, U2.B4, U2.B5, U2.B6, U2.B7, U2.B13, U2.B17, U2.B21, U2.C4, U2.C7, U2.C15, U2.C16, U2.C17, U2.C23, U2.D2, U2.D21, U2.D22, U2.D23, U2.E2, U2.E21, U2.E22, U2.E23, U2.F21, U2.F22, U2.F23, U2.G2, U2.G21, U2.G23, U2.H21, U2.H22, U2.H23, U2.J21, U2.J22, U2.J23, U2.K2, U2.K21, U2.K22, U2.K23, U2.L21, U2.L22, U2.L23, U2.M21, U2.M22, U2.N21, U2.N22, U2.P1, U2.P2, U2.P3, U2.P21, U2.P22, U2.R3, U2.R21, U2.R22, U2.T21, U2.T22, U2.T23, U2.U2, U2.U21, U2.U22, U2.U23, U2.V21, U2.V22, U2.W21, U2.W22, U2.W23, U2.Y2, U2.Y21, U2.Y22, U2.Y23, U3.1, U4.3
unnamed: C5.1, L1.2, L2.1
unnamed: D3.2, R3.1
unnamed: D4.2, R4.1
unnamed: D6.2, R5.1
unnamed: D7.2, R6.1
unnamed: D8.2, R7.1
unnamed: U2.AC16, U2.AC17
unnamed: U2.M23, U2.N23

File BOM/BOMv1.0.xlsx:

Reference | Description | Quantity | Value | Source | Footprint | Price/pc | Price/Total | Notes
C3 C2 C5 C1 | Capacitors - 100nF | 4 | 100nF | https://www.digikey.com/product-detail/en/yageo/CC0603KRX7R6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 | Capacitor_SMD:C_0603_1608Metric | 0.12 | 0.48
C4 C7 C6 | Capacitors - 10uF | 3 | 10uF | https://www.digikey.com/product-detail/en/yageo/CC0603KRX5R6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 | Capacitor_SMD:C_0603_1608Metric | 0.28999999999999998 | 0.86999999999999988
D2 D1 D5 | Schottky Diodes | 3 | MBR0520LT | https://www.digikey.com/product-detail/en/micro-commercial-c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 | Diode_SMD:D_SOD-123 | 0.41 | 1.23
D3 D4 D6 D8 D7 | Blue LEDs - 10mA | 5 | LED | https://www.digikey.com/product-detail/en/vishay-semiconduct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 | LED_SMD:LED_0603_1608Metric | 1.19 | 5.9499999999999993
FL1 | USB Protection | 1 | ECMF02-2AMX6 | https://www.digikey.com/product-detail/en/stmicroelectronics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 | Package_DFN_QFN:ST_UQFN-6L_1.5x1.7mm_Pitch0.5mm | 0.48 | 0.48
J1 | MicroUSB connector | 1 | USB_B_Micro | https://www.digikey.com/product-detail/en/molex/1050170001/W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 | Connector_USB:USB_Micro-B_Molex-105017-0001 | 0.91 | 0.91
J2 | Rpi connector 2*20 2.54mm | 1 | raspberrypi_hat_OX40HAT | https://www.digikey.com/product-detail/en/adafruit-industrie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 | Connector_PinSocket_2.54mm:PinSocket_2x20_P2.54mm_Vertical | 2.5 | 2.5
J3, J4 | SMA right angle connector | 2 | Conn_Coaxial | https://www.digikey.com/product-detail/en/amphenol-rf/132136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 | Connector_Coaxial:SMA_Amphenol_132203-12_Horizontal | 7.94 | 15.88
J5 | events&pps connector 1*4 2.54mm | 1 | Conn_01x04_Male | https://www.digikey.com/product-detail/en/molex/0022122041/2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 | Connector_PinHeader_2.54mm:PinHeader_1x04_P2.54mm_Horizontal | 0.74 | 0.74
J6 | FTDI connector 1*6 2.54mm | 1 | Conn_01x06_Male | https://www.digikey.com/product-detail/en/molex/0022122061/2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 | Connector_PinHeader_2.54mm:PinHeader_1x06_P2.54mm_Horizontal | 1.1000000000000001 | 1.1000000000000001
J7 | Ext pwr src connector 1*2 2.54mm | 1 | Conn_01x02_Male | https://www.digikey.com/product-detail/en/molex/0022122021/2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 | Connector_PinHeader_2.54mm:PinHeader_1x02_P2.54mm_Horizontal | 0.47 | 0.47
JP1 JP2 | Jumper connectors 1*3 2.00mm | 2 | Jumper_NC_Dual | https://www.digikey.com/product-detail/en/adam-tech/2PH1-03-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 | Connector_PinHeader_2.00mm:PinHeader_1x03_P2.00mm_Vertical | 0.11 | 0.22
L1 L2 | Inductors | 2 | L | https://www.digikey.com/product-detail/en/w%C3%BCrth-elektro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 | Inductor_SMD:L_0603_1608Metric | 0.2 | 0.4
P1 | Antenna protection | 1 | TVS | https://www.digikey.com/product-detail/en/littelfuse-inc/SES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 | Diode_SMD:D_0402_1005Metric | 0.61 | 0.61
R3 R4 R5 R6 R7 | LED resistors - 330Ohm | 5 | R330 | https://www.digikey.com/product-detail/en/panasonic-electron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 | Resistor_SMD:R_0603_1608Metric | 0.1 | 0.5
U1 | Level shifter (1V8-3V3) | 1 | SN74AVC4T245PW | https://www.digikey.com/product-detail/en/texas-instruments/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 | Package_SO:TSSOP-16_4.4x5mm_P0.65mm | 0.87 | 0.87
U3 | Voltage Regulator - 3V3 | 1 | LD1117S33TR_SOT223 | https://www.digikey.com/product-detail/en/stmicroelectronics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 | Package_TO_SOT_SMD:SOT-223-3_TabPin2 | 0.41 | 0.41
U4 | 3-state buffer | 1 |  | https://www.digikey.com/product-detail/en/texas-instruments/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 | Package_TO_SOT_SMD:SOT-553 | 0.39 | 0.39
Unassembled | Unconnected Jumpers 1*2 2.00mm | 2 |  | https://www.digikey.com/product-detail/en/sullins-connector-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 |  | 0.13 | 0.26 | Separate components
U2 | Mosaic-X5 | 1 | Mosaic_v0.12 | Septentrio | mLAYOUT:MinROSv0.12 | 0 | 0 | provided by SNN
 |  |  |  |  |  | Total price | 34.269999999999989

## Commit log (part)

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2020-10-06 Rename HATv1.0.kicad_pcb to Project_files/HATv1.0.kicad_pcb
2020-10-06 Rename HATv1.0.pro to Project_files/HATv1.0.pro
2020-10-06 Rename HATv1.0.sch to Project_files/HATv1.0.sch
2020-10-06 Rename Project_files/HATv1.0.kicad_pcb to KiCAD_files/HATv1.0.kicad_pcb
2020-10-06 Rename Project_files/HATv1.0.pro to Project_files/KiCAD_files/HATv1.0.pro
2020-10-06 Rename Project_files/KiCAD_files/HATv1.0.pro to KiCAD_files/HATv1.0.pro
2020-10-06 Rename Project_files/HATv1.0.sch to KiCAD_files/HATv1.0.sch
2020-10-06 Create a
2020-10-07 Rename mosaic-X5.lib to mosaic_design_components/mosaic-X5.lib
2020-10-08 Renaming folder
    Renaming folder there was a typo
2020-10-08 Adding files for documentation
2020-10-08 renaming file
2020-10-08 Updated pic
2020-10-08 Updating pic
2020-10-09 New pictures
2020-10-16 Updating picture logo
2020-10-16 Updating pictures
2020-10-16 update project
2020-10-16 update layout
2020-10-18 update project library
2020-10-18 update schematic
2021-03-07 add mosaicHAT + BT breadboard view
2021-03-08 mosaicHAT Raspberry Pi connections expansion
2021-03-21 Add files via upload
    add mosaicHAT_station
2021-04-29 add fritzing part & mosaicHAT SVG
2021-11-10 Update README.md
    https://forum.kicad.info/t/warning-avoid-all-links-to-kicad-pcb-org-use-kicad-org/31521
2024-07-09 Delete References/mosaic_hardware_manual_v1.3.0.pdf
    old reference manual, most up-to-date material on Septentrio website
